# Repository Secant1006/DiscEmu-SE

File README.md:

# DiscEmu-SE

Emulates USB optical drive and USB floppy drive (now cheaper to produce)

# Firmware

By [slzKud](https://github.com/slzKud). Currently not available due to the early stage of development.

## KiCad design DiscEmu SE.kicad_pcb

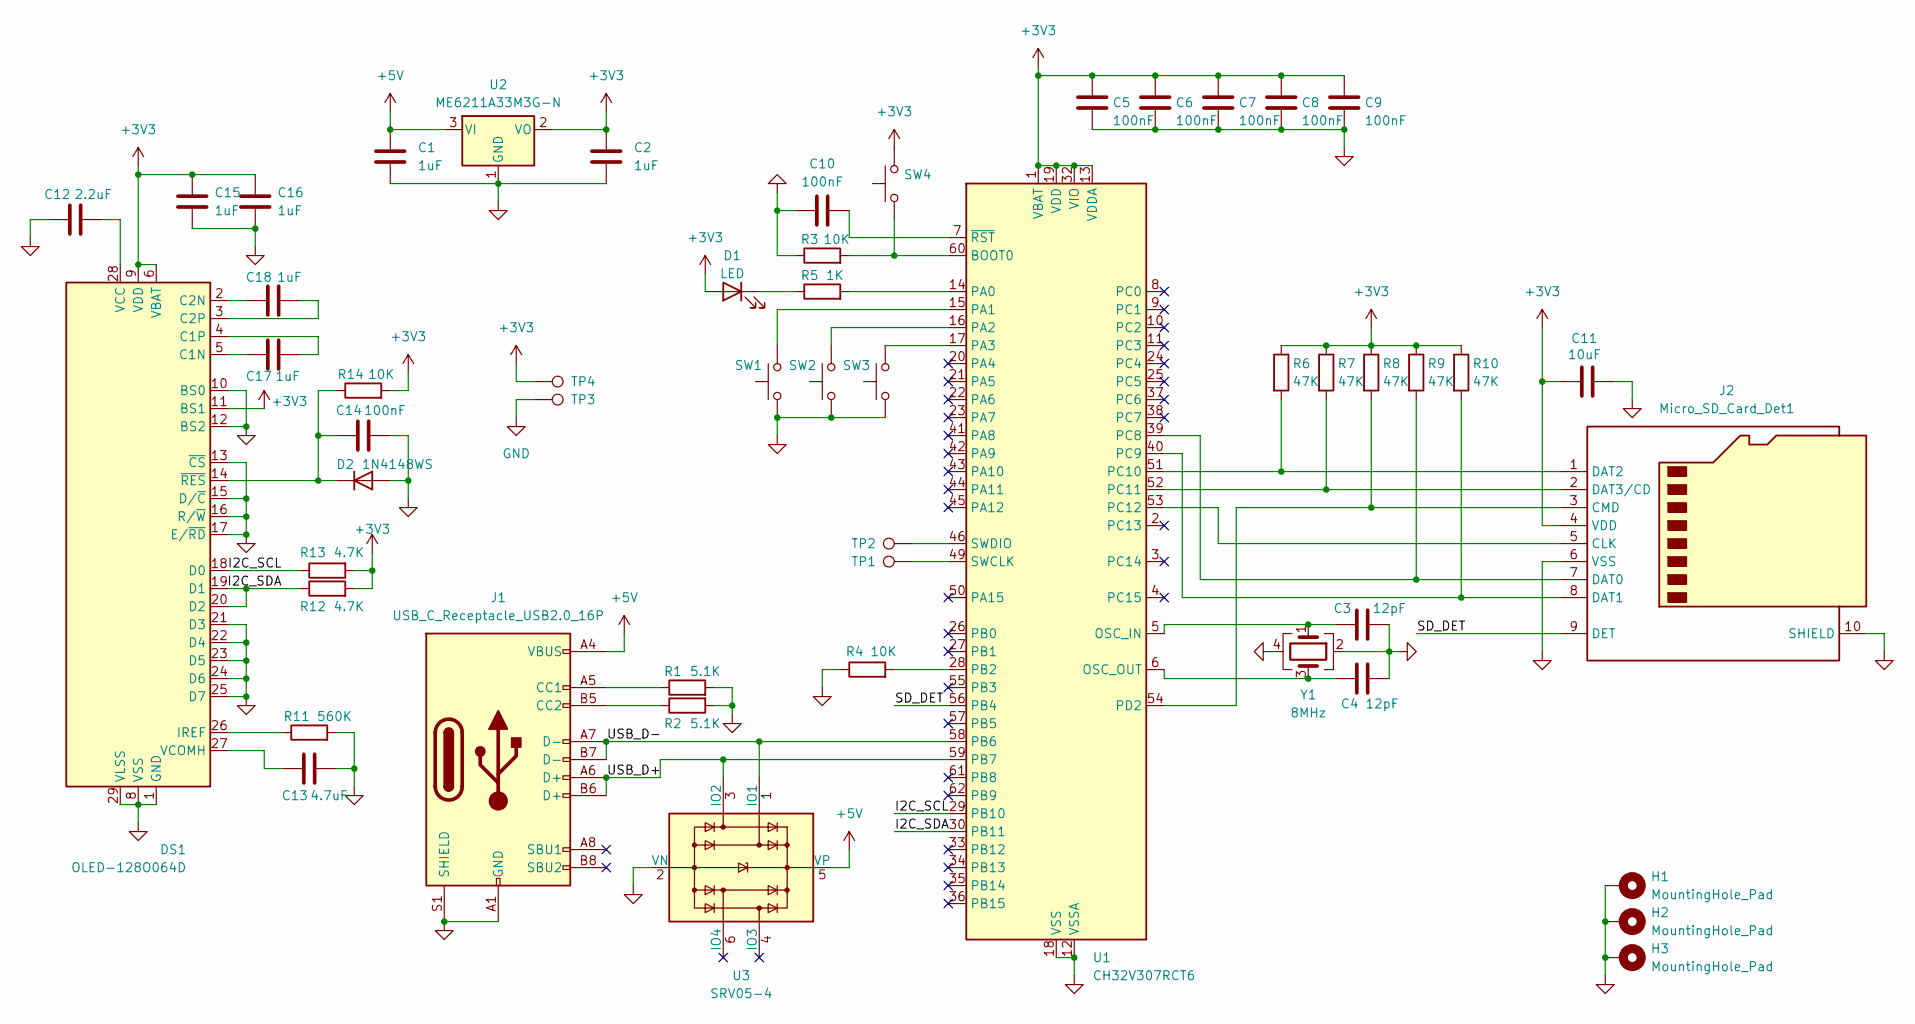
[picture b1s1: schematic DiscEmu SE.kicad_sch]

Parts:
C1, C2, C15, C16, C17, C18: 1uF; C_0603_1608Metric
C3, C4: 12pF; C_0603_1608Metric
C5, C6, C7, C8, C9, C10, C14: 100nF; C_0603_1608Metric
C11: 10uF; C_0603_1608Metric
C12: 2.2uF; C_0603_1608Metric
C13: 4.7uF; C_0603_1608Metric
D1: LED; LED_0603_1608Metric
D2: 1N4148WS; D_SOD-323
DS1: OLED-128O064D
H1, H2, H3: MountingHole_Pad; MountingHole_2.2mm_M2_Pad
J1: USB_C_Receptacle_USB2.0_16P; USB_C_Receptacle_XKB_U262-16XN-4BVC11
J2: Micro_SD_Card_Det1; TF-SMD_XKTF-015-N
R1, R2: 5.1K; R_0603_1608Metric
R3, R4, R14: 10K; R_0603_1608Metric
R5: 1K; R_0603_1608Metric
R6, R7, R8, R9, R10: 47K; R_0603_1608Metric
R11: 560K; R_0603_1608Metric
R12, R13: 4.7K; R_0603_1608Metric
SW1, SW2, SW3: SW_Push; SW_Push_1P1T_XKB_TS-1187A
SW4: SW_Push; SW_Push_SPST_NO_Alps_SKRK
TP1, TP2, TP3, TP4: TestPoint; TestPoint_Pad_D1.0mm
U1: CH32V307RCT6; LQFP-64_10x10mm_P0.5mm
U2: ME6211A33M3G-N; SOT-23-3
U3: SRV05-4; SOT-23-6
Y1: 8MHz; Crystal_SMD_3225-4Pin_3.2x2.5mm

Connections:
+3V3: C2.1, C5.1, C6.1, C7.1, C8.1, C9.1, C11.1, C15.1, C16.1, D1.2 (A), DS1.6 (VBAT), DS1.9 (VDD), DS1.11 (BS1), J2.4 (VDD), R6.1, R7.1, R8.1, R9.1, R10.1, R12.2, R13.2, R14.2, SW4.2, TP4.1, U1.1 (VBAT), U1.13 (VDDA), U1.19 (VDD), U1.32 (VIO), U1.48 (VDD), U1.64 (VIO), U2.2 (VO)
+5V: C1.1, J1.A4 (VBUS), J1.A9 (VBUS), J1.B4 (VBUS), J1.B9 (VBUS), U2.3 (VI), U3.5 (VP)
/I2C_SCL: DS1.18 (D0), R13.1, U1.29 (PB10)
/I2C_SDA: DS1.19 (D1), DS1.20 (D2), R12.1, U1.30 (PB11)
/SD_DET: J2.9 (DET), U1.56 (PB4)
/USB_D+: J1.A6 (D+), J1.B6 (D+), U1.59 (PB7), U3.3 (IO2)
/USB_D-: J1.A7 (D-), J1.B7 (D-), U1.58 (PB6), U3.1 (IO1)
GND: C1.2, C2.2, C3.2, C4.2, C5.2, C6.2, C7.2, C8.2, C9.2, C10.1, C11.2, C12.1, C13.2, C14.2, C15.2, C16.2, D2.2 (A), DS1.1 (GND), DS1.8 (VSS), DS1.10 (BS0), DS1.12 (BS2), DS1.13 (~CS), DS1.15 (D/~C), DS1.16 (R/~W), DS1.17 (E/~RD), DS1.21 (D3), DS1.22 (D4), DS1.23 (D5), DS1.24 (D6), DS1.25 (D7), DS1.29 (VLSS), DS1.30 (GND), H1.1, H2.1, H3.1, J1.A1 (GND), J1.A12 (GND), J1.B1 (GND), J1.B12 (GND), J1.S1 (SHIELD), J2.6 (VSS), J2.10 (SHIELD), R1.2, R2.2, R3.1, R4.1, R11.2, SW1.1, SW2.1, SW3.1, TP3.1, U1.12 (VSSA), U1.18 (VSS), U1.31 (VSS), U1.47 (VSS), U1.63 (VSS), U2.1 (GND), U3.2 (VN), Y1.2, Y1.4
unnamed: D1.1 (K), R5.1
unnamed: C14.1, D2.1 (K), DS1.14 (~RES), R14.1
unnamed: C17.1, DS1.5 (C1N)
unnamed: C17.2, DS1.4 (C1P)
unnamed: C18.1, DS1.2 (C2N)
unnamed: C18.2, DS1.3 (C2P)
unnamed: DS1.26 (IREF), R11.1
unnamed: C12.2, DS1.28 (VCC)
unnamed: C13.1, DS1.27 (VCOMH)
unnamed: J1.A5 (CC1), R1.1
unnamed: J1.B5 (CC2), R2.1
unnamed: J2.5 (CLK), U1.53 (PC12)
unnamed: J2.3 (CMD), R8.2, U1.54 (PD2)
unnamed: J2.7 (DAT0), R9.2, U1.39 (PC8)
unnamed: J2.8 (DAT1), R10.2, U1.40 (PC9)
unnamed: J2.1 (DAT2), R6.2, U1.51 (PC10)
unnamed: J2.2 (DAT3/CD), R7.2, U1.52 (PC11)
unnamed: R3.2, SW4.1, U1.60 (BOOT0)
unnamed: C3.1, U1.5 (OSC_IN), Y1.1
unnamed: C4.1, U1.6 (OSC_OUT), Y1.3
unnamed: R5.2, U1.14 (PA0)
unnamed: SW1.2, U1.15 (PA1)
unnamed: SW2.2, U1.16 (PA2)
unnamed: SW3.2, U1.17 (PA3)
unnamed: R4.2, U1.28 (PB2)
unnamed: TP1.1, U1.49 (SWCLK)
unnamed: TP2.1, U1.46 (SWDIO)
unnamed: C10.2, U1.7 (~RST)

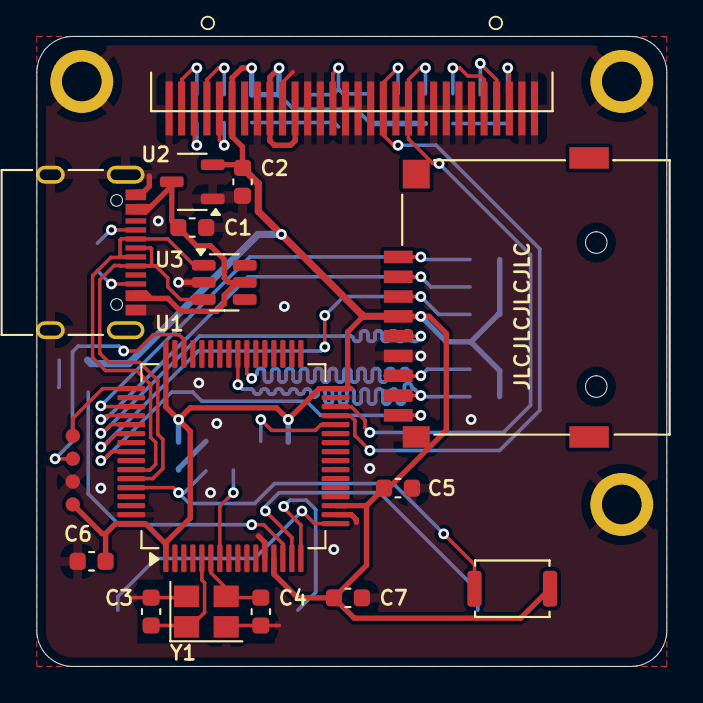
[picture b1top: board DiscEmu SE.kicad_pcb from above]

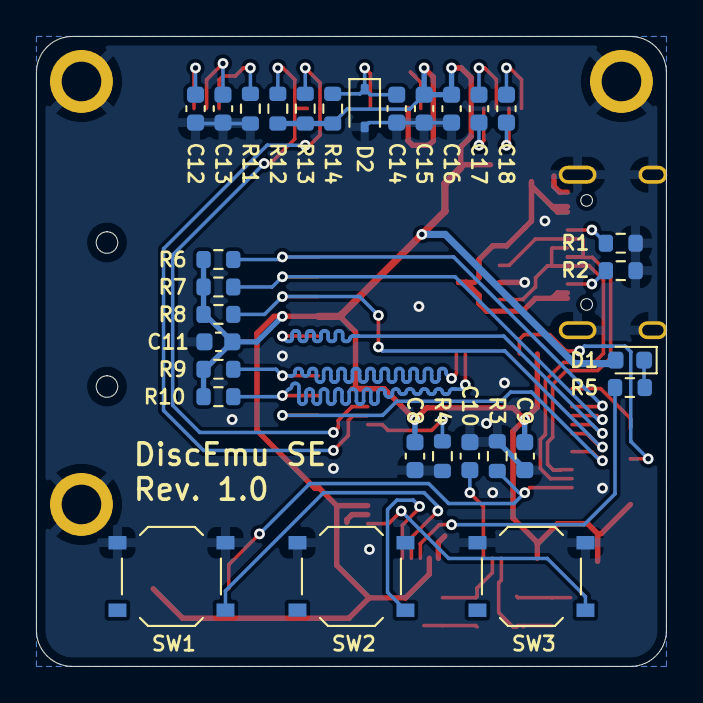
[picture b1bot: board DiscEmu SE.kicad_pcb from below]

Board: 2 copper layers, 35.0 x 35.0 mm, 52 parts (30 on the bottom side), 36 nets.

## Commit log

2026-05-26 Release 1.0
2026-05-26 Fix readme
2026-05-27 Modify gitignore
